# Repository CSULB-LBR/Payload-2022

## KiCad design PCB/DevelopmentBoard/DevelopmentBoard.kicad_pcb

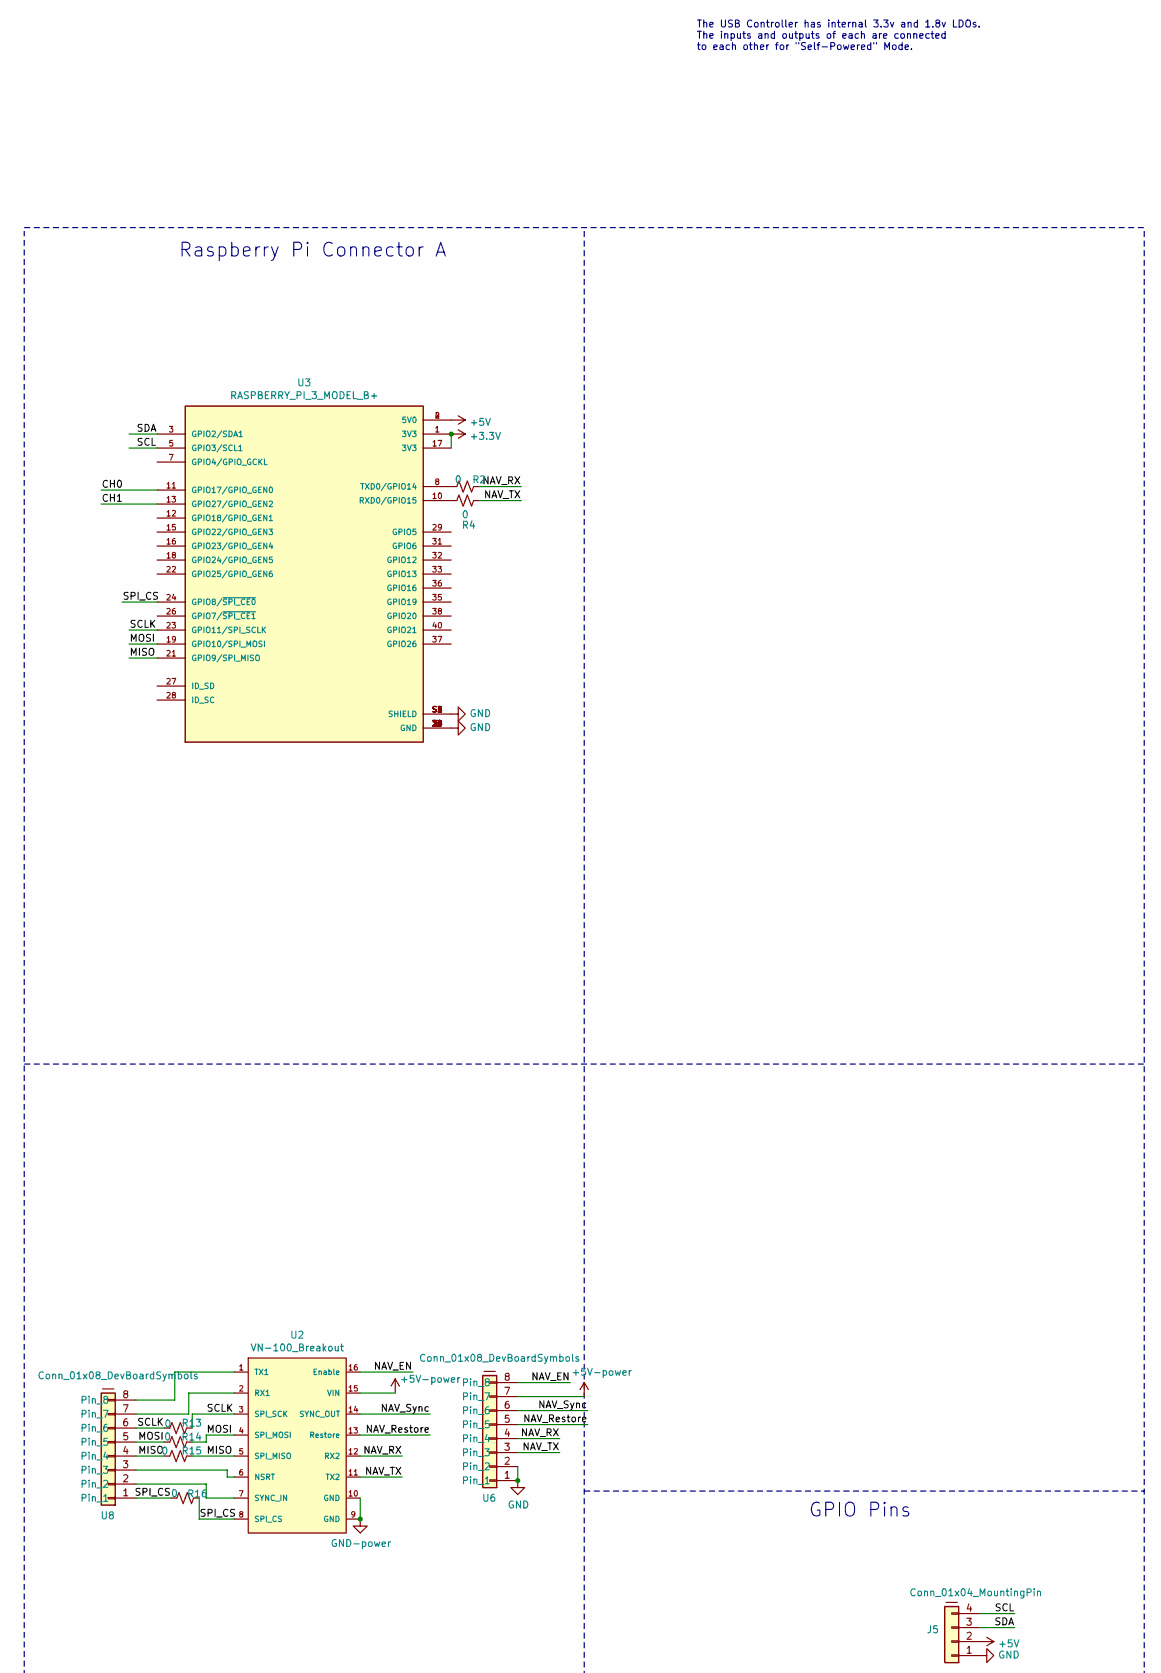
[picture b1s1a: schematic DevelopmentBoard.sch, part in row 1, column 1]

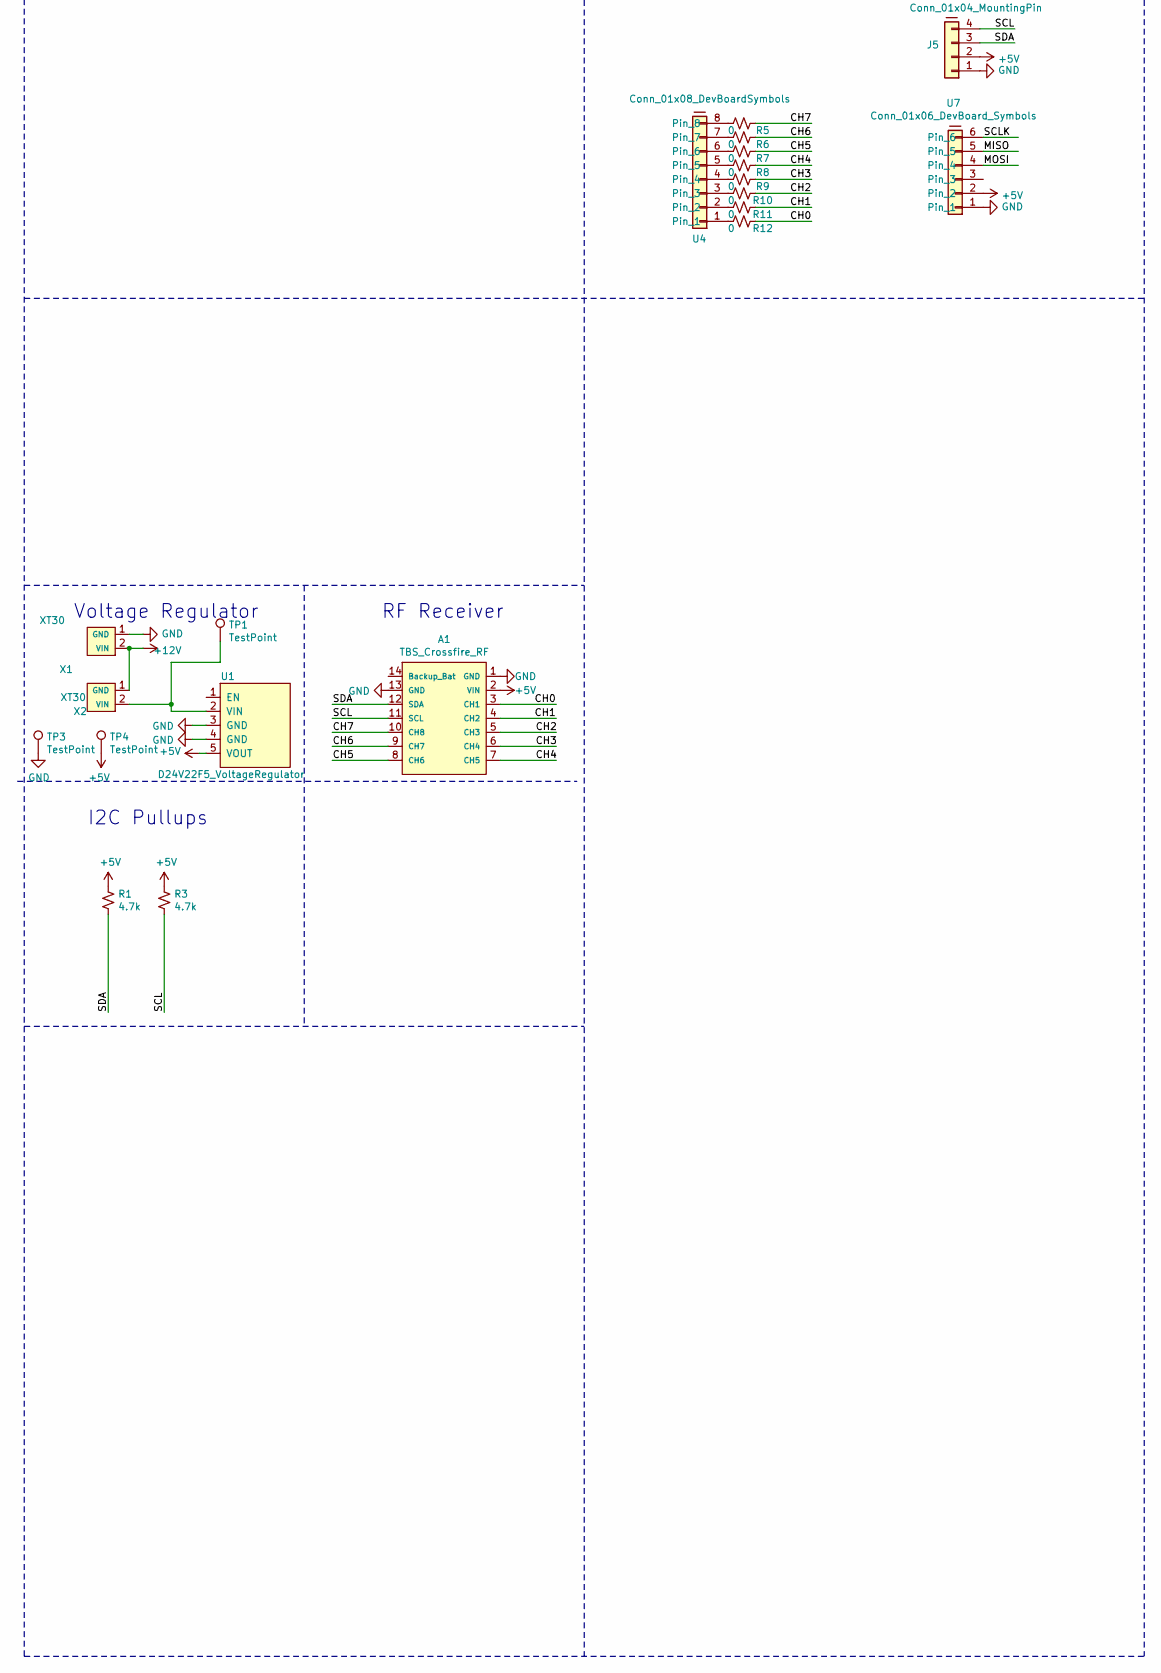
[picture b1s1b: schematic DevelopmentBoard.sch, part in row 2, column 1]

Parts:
A1: TBS_Crossfire_RF
J5: Conn_01x04_MountingPin; PinHeader_1x04_P2.54mm_Vertical
R1, R3: 4.7k; 0603
R2, R4, R5, R6, R7, R8, R9, R10, R11, R12, R13, R14, R15, R16: 0; 0603
TP1, TP3, TP4: TestPoint; TestPoint_Pad_D2.5mm
U1: D24V22F5_VoltageRegulator
U2: VN-100_Breakout; VN-100Breakout
U3: RASPBERRY_PI_3_MODEL_B+; MODULE_RASPBERRY_PI_3_MODEL_B+; PARTREV 1.0
U4, U6, U8: Conn_01x08_DevBoardSymbols; PinHeader_1x08_P2.54mm_Vertical
U7: Conn_01x06_DevBoard_Symbols; PinHeader_1x06_P2.54mm_Vertical
X1, X2: XT30; AMASS_XT30U-M_1x02_P5.0mm_Vertical

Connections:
+3V3: U3.1 (3V3), U3.17 (3V3)
+12V: X1.2 (VIN), X2.1 (GND)
/CH0: A1.3 (CH1), R12.2, U3.11 (GPIO17/GPIO_GEN0)
/CH1: A1.4 (CH2), R11.2, U3.13 (GPIO27/GPIO_GEN2)
/CH2: A1.5 (CH3), R10.2
/CH3: A1.6 (CH4), R9.2
/CH4: A1.7 (CH5), R8.2
/CH5: A1.8 (CH6), R7.2
/CH6: A1.9 (CH7), R6.2
/CH7: A1.10 (CH8), R5.2
/MISO: R15.1, R15.2, U2.5 (SPI_MISO), U3.21 (GPIO9/SPI_MISO), U7.5, U8.4
/MOSI: R14.1, R14.2, U2.4 (SPI_MOSI), U3.19 (GPIO10/SPI_MOSI), U7.4, U8.5
/NAV_EN: U2.16 (Enable), U6.8
/NAV_RX: R2.1, U2.12 (RX2), U6.4
/NAV_Restore: U2.13 (Restore), U6.5
/NAV_Sync: U2.14 (SYNC_OUT), U6.6
/NAV_TX: R4.1, U2.11 (TX2), U6.3
/SCL: A1.11 (SCL), J5.4, R3.2, U3.5 (GPIO3/SCL1)
/SCLK: R13.1, R13.2, U2.3 (SPI_SCK), U3.23 (GPIO11/SPI_SCLK), U7.6, U8.6
/SDA: A1.12 (SDA), J5.3, R1.2, U3.3 (GPIO2/SDA1)
/SPI_CS: R16.1, R16.2, U2.8 (SPI_CS), U3.24 (GPIO8/~SPI_CE0~), U8.1
unnamed: R2.2, U3.8 (TXD0/GPIO14)
unnamed: R4.2, U3.10 (RXD0/GPIO15)
unnamed: R5.1, U4.8
unnamed: R6.1, U4.7
unnamed: R7.1, U4.6
unnamed: R8.1, U4.5
unnamed: R9.1, U4.4
unnamed: R10.1, U4.3
unnamed: R11.1, U4.2
unnamed: R12.1, U4.1
unnamed: TP1.1, U1.2 (VIN), X2.2 (VIN)
unnamed: U2.1 (TX1), U8.8
unnamed: U2.2 (RX1), U8.7
unnamed: U2.6 (NSRT), U8.3
unnamed: U2.7 (SYNC_IN), U8.2

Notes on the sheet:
The USB Controller has internal 3.3v and 1.8v LDOs. The inputs and outputs of each are connected to each other for "Self-Powered" Mode.
Raspberry Pi Connector A
Voltage Regulator
RF Receiver
GPIO Pins
I2C Pullups

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
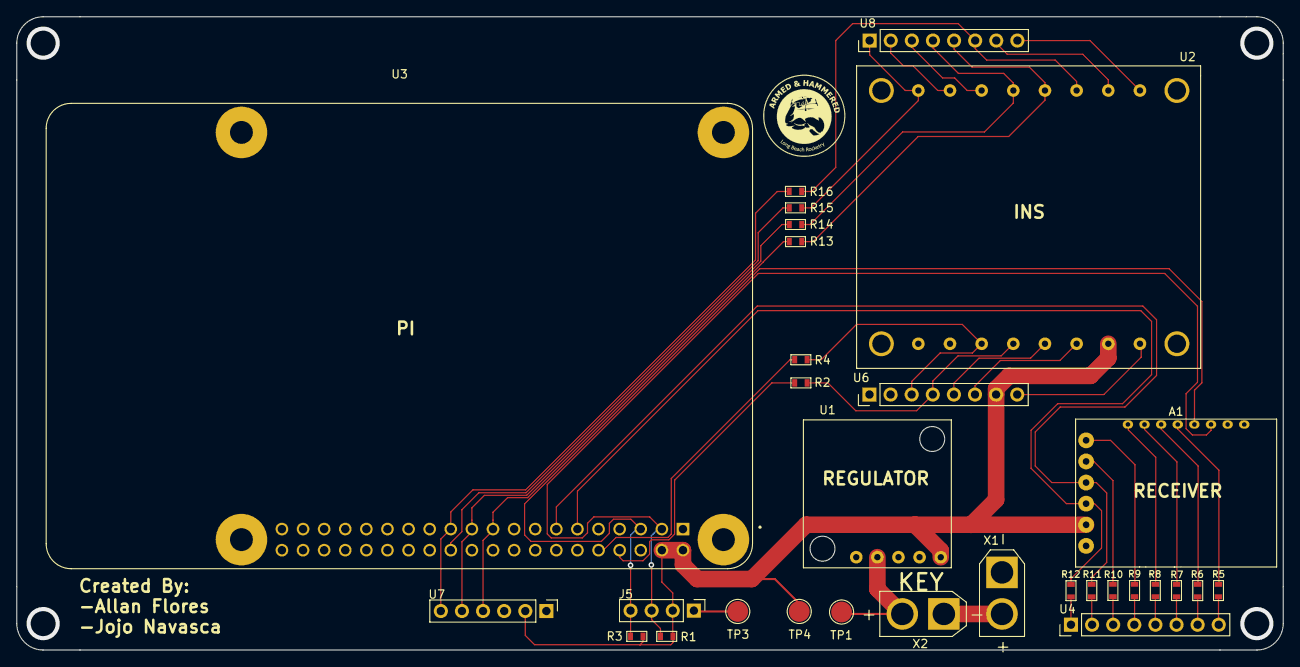
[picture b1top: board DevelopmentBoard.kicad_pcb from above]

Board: 2 copper layers, 152.4 x 76.2 mm, 30 parts (0 on the bottom side), 38 nets.

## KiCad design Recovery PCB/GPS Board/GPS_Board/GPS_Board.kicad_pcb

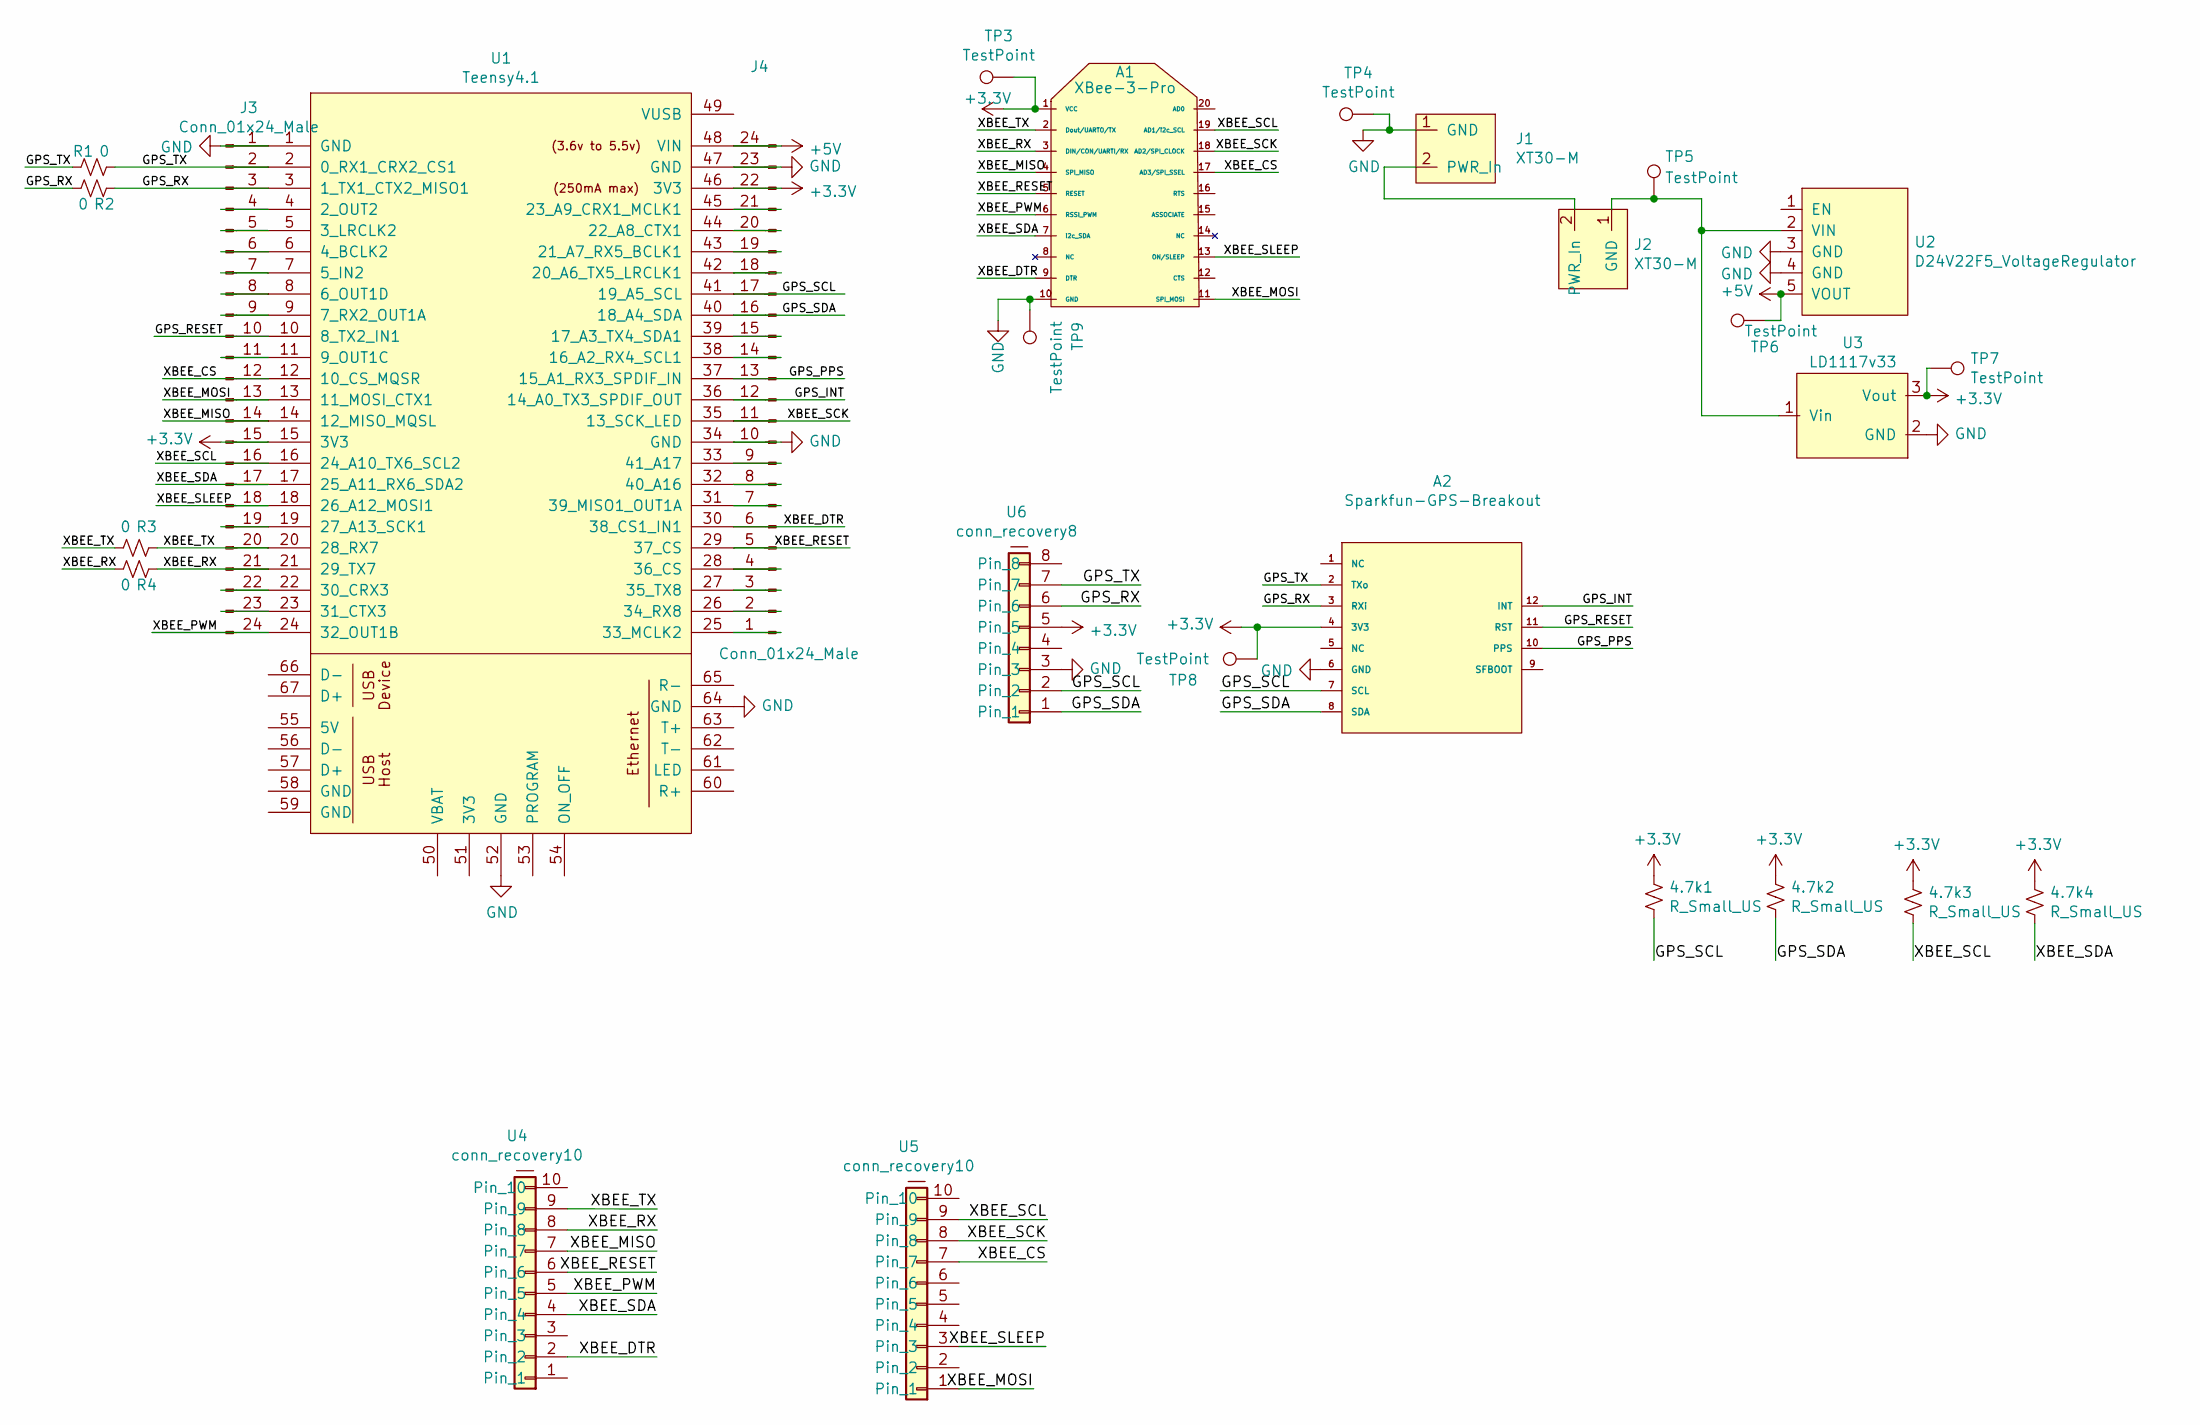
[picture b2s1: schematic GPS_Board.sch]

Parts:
4.7k1, 4.7k2, 4.7k3, 4.7k4: R_Small_US; 0603
A1: XBee-3-Pro; XBEE-20_THT
A2: Sparkfun-GPS-Breakout; Sparkfun-GPS-ZOE-M8Q-Breakout
J1, J2: XT30-M; AMASS_XT30U-M_1x02_P5.0mm_Vertical
J3, J4: Conn_01x24_Male; SMD_Connector_1x24
R1, R2: 0; 0603
R3, R4: 0; 0603_BACK
TP3, TP4, TP5, TP6, TP7, TP8, TP9: TestPoint; TestPoint_Pad_D2.0mm
U1: Teensy4.1; Teensy41
U2: D24V22F5_VoltageRegulator
U3: LD1117v33; TO-220-3_Horizontal_TabDown
U4, U5: conn_recovery10; PinHeader_1x10_P2.54mm_Vertical
U6: conn_recovery8; PinHeader_1x08_P2.54mm_Vertical

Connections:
+3V3: 4.7k1.1, 4.7k2.1, 4.7k3.1, 4.7k4.1, A1.1 (VCC), A2.4 (3V3), J3.15, J4.22, TP3.1, TP7.1, TP8.1, U1.15 (3V3), U1.46 (3V3), U3.3 (Vout), U6.5
+5V: J4.24, TP6.1, U1.48 (VIN), U2.5 (VOUT)
/GPS_INT: A2.12 (INT), J4.12, U1.36 (14_A0_TX3_SPDIF_OUT)
/GPS_PPS: A2.10 (PPS), J4.13, U1.37 (15_A1_RX3_SPDIF_IN)
/GPS_RESET: A2.11 (RST), J3.10, U1.10 (8_TX2_IN1)
/GPS_RX: A2.3 (RXi), J3.3, R2.1, R2.2, U1.3 (1_TX1_CTX2_MISO1), U6.6
/GPS_SCL: 4.7k1.2, A2.7 (SCL), J4.17, U1.41 (19_A5_SCL), U6.2
/GPS_SDA: 4.7k2.2, A2.8 (SDA), J4.16, U1.40 (18_A4_SDA), U6.1
/GPS_TX: A2.2 (TXo), J3.2, R1.1, R1.2, U1.2 (0_RX1_CRX2_CS1), U6.7
/XBEE_CS: A1.17 (AD3/SPI_SSEL), J3.12, U1.12 (10_CS_MQSR), U5.7
/XBEE_DTR: A1.9 (DTR), J4.6, U1.30 (38_CS1_IN1), U4.2
/XBEE_MISO: A1.4 (SPI_MISO), J3.14, U1.14 (12_MISO_MQSL), U4.7
/XBEE_MOSI: A1.11 (SPI_MOSI), J3.13, U1.13 (11_MOSI_CTX1), U5.1
/XBEE_PWM: A1.6 (RSSI_PWM), J3.24, U1.24 (32_OUT1B), U4.5
/XBEE_RESET: A1.5 (RESET), J4.5, U1.29 (37_CS), U4.6
/XBEE_RX: A1.3 (DIN/CON/UARTI/RX), J3.21, R4.1, R4.2, U1.21 (29_TX7), U4.8
/XBEE_SCK: A1.18 (AD2/SPI_CLOCK), J4.11, U1.35 (13_SCK_LED), U5.8
/XBEE_SCL: 4.7k3.2, A1.19 (AD1/i2c_SCL), J3.16, U1.16 (24_A10_TX6_SCL2), U5.9
/XBEE_SDA: 4.7k4.2, A1.7 (i2c_SDA), J3.17, U1.17 (25_A11_RX6_SDA2), U4.4
/XBEE_SLEEP: A1.13 (ON/SLEEP), J3.18, U1.18 (26_A12_MOSI1), U5.3
/XBEE_TX: A1.2 (Dout/UARTO/TX), J3.20, R3.1, R3.2, U1.20 (28_RX7), U4.9
GND: A1.10 (GND), A2.6 (GND), J1.1 (GND), J3.1, J4.10, J4.23, TP4.1, TP9.1, U1.1 (GND), U1.34 (GND), U1.47 (GND), U1.52 (GND), U1.64 (GND), U2.3 (GND), U2.4 (GND), U3.2 (GND), U6.3
unnamed: J1.2 (PWR_In), J2.2 (PWR_In)
unnamed: J2.1 (GND), TP5.1, U2.2 (VIN), U3.1 (Vin)
unnamed: J3.4, U1.4 (2_OUT2)
unnamed: J3.5, U1.5 (3_LRCLK2)
unnamed: J3.6, U1.6 (4_BCLK2)
unnamed: J3.7, U1.7 (5_IN2)
unnamed: J3.8, U1.8 (6_OUT1D)
unnamed: J3.9, U1.9 (7_RX2_OUT1A)
unnamed: J3.11, U1.11 (9_OUT1C)
unnamed: J3.19, U1.19 (27_A13_SCK1)
unnamed: J3.22, U1.22 (30_CRX3)
unnamed: J3.23, U1.23 (31_CTX3)
unnamed: J4.1, U1.25 (33_MCLK2)
unnamed: J4.2, U1.26 (34_RX8)
unnamed: J4.3, U1.27 (35_TX8)
unnamed: J4.4, U1.28 (36_CS)
unnamed: J4.7, U1.31 (39_MISO1_OUT1A)
unnamed: J4.8, U1.32 (40_A16)
unnamed: J4.9, U1.33 (41_A17)
unnamed: J4.14, U1.38 (16_A2_RX4_SCL1)
unnamed: J4.15, U1.39 (17_A3_TX4_SDA1)
unnamed: J4.18, U1.42 (20_A6_TX5_LRCLK1)
unnamed: J4.19, U1.43 (21_A7_RX5_BCLK1)
unnamed: J4.20, U1.44 (22_A8_CTX1)
unnamed: J4.21, U1.45 (23_A9_CRX1_MCLK1)

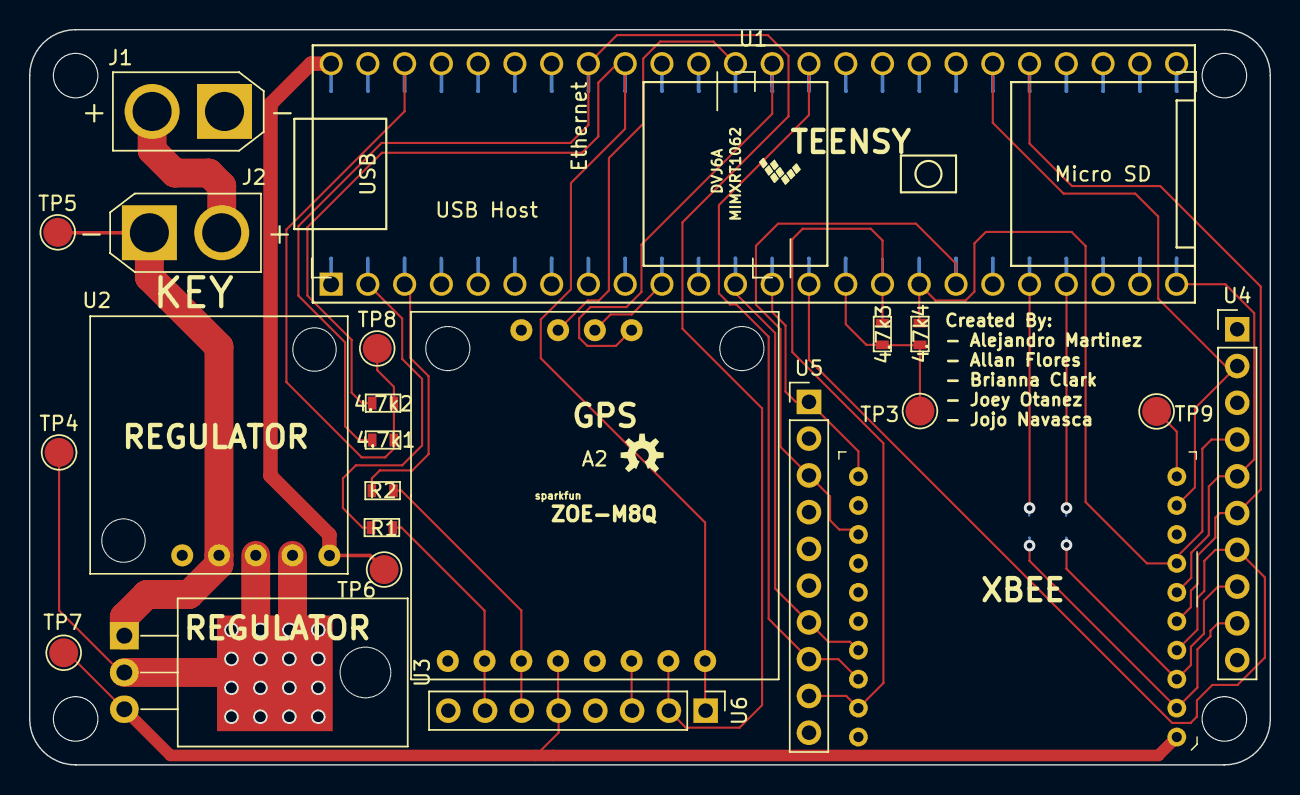
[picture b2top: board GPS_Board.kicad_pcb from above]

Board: 2 copper layers, 85.7 x 50.8 mm, 27 parts (0 on the bottom side), 47 nets.

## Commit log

2021-10-01 initial folder structure
2021-10-01 Created FlightBoard folder
2021-10-02 VN-100
    Made VN-100 Symbol
2021-10-02 d24v22f5 symbol added
2021-10-02 Deleted test symbols
2021-10-04 Relabeled GND on Voltage Regulator Symbol
2021-10-04 Added Voltage Regulator footprint
2021-10-04 Started VN-100 Footprint
2021-10-04 Added ground pin to Polololololol Board :)
2021-10-04 Pololooooo board for 6th ground pin dimension verified
2021-10-04 Labeled VN-100 Footprint Pins
2021-10-04 Added missing pins to VN-100 footprint
2021-10-04 Finished all pins for VN-100
2021-10-05 Added XT30 and TBS RF Module symbols and footprints
2021-10-05 FIx XT-30
    Changed gnd number
2021-10-07 Added Micro-USB and Pi CM4 symbol, and Pi CM4 footprint
2021-10-07 Micro USB
    Adjusted Micro USB symbol
2021-10-07 Edited PI CM4 symbol
2021-10-07 Started schematic capture
2021-10-07 Schematic Capture for RF module
2021-10-07 Placed Micro-USB symbol on schematic
2021-10-07 Deleted redundant RPI symbol library
2021-10-07 USB Pins
    Found and connected the USB pins on pins 103 & 105
2021-10-09 Created VN-100 Breakout project
2021-10-09 Cleaned up VN-100 pins
    Removed some extra pins
2021-10-09 Barometer
    Added Barometer Symbol
2021-10-09 Altimeter
    Added footprint of Altimeter with screholes
2021-10-10 Testing potential layout for board
2021-10-10 Updated pin numbering on VN-100 Breakout symbol
2021-10-11 Updated Altimeter/Barometer footprint, started VN-100 Breakout schematic capture
2021-10-11 VN-100 Breakout Created Label Connection
2021-10-12 VN-100 Board Layout started
2021-10-12 VN-100 edited
    Connected some traces in VN-100
2021-10-12 Reworked some traces from Martin
2021-10-12 Connected ground to pads
2021-10-12 Finished VN-100 Breakout Board. Removed USB from DevBoard Schematic
2021-10-13 Updated Dev Board Schematic
2021-10-13 Devboard changes(UART & SPI)
2021-10-13 Started Dev Board Layout
2021-10-13 Routed Test Traces for important signals
2021-10-13 Moved Altimeter and RF module for better I2C routing
2021-10-13 Added test points
2021-10-13 Edited 5v Traces
    Edited 5v traces on PCB
2021-10-14 Readjusted traces
2021-10-14 Added footprint courtyards
2021-10-14 Created Courtyard Voltage Regulator
2021-10-14 Sized traces. Moved USB connector. Uncrossed all signals.
2021-10-14 PCB Traces checked
2021-10-15 Traced matched USB D+ and D-
2021-10-16 Adjusted USB traces
2021-10-16 Added Step Files for RF Module and Voltage Regulator
2021-10-16 Rematched traces with Differential Pair tool. Added Step Files.
2021-10-16 added cm4 step model to dev board
2021-10-16 file system modifications for multi user work and created vn-100 breakout step
2021-10-16 Update fp-info-cache
2021-10-16 Routed traces for updated VN-100 breakout
2021-10-16 Changed VN-100 Breakout
2021-10-16 fixed vn-100 layer count and fill
2021-10-16 vectornav logo but its fps killer
2021-10-16 cant get rid of fps killer ss
2021-10-16 recerting before fps killer
2021-10-16 repaired after logo incident
2021-10-16 Grounded Pi Compute Module
2021-10-16 adjusted vn breakout
2021-10-16 fixed vectornav logo stuff
2021-10-16 breakout 3d model
2021-10-16 Updated footprint and symbol path
2021-10-16 added silkscreening, board outline, and fixed vn-100 carrier socket,plus renders
    NEEDS A MEME
2021-10-16 added grove 3d model
2021-10-20 step file locations changed for compatibility
2021-10-22 adding ethernet and UART breakout shrinking width of board with necessary rearrangement
2021-10-22 giving up on ethernet for now, added a couple of open source breakout designs for reference
2021-10-23 changed models directory again
2021-10-23 ladybug happy :)
2021-10-23 ladybug more happier
2021-10-23 Reassociated 3D files
2021-10-23 revert
2021-10-23 got it to make a step file literally no idea how
2021-10-23 zippedupthedingus
2021-10-23 tidying
2021-10-27 credits
2021-12-02 Removed "PayloadSymbols" Folder, consolidated symbols and footprints into DevelopmentBoard Folder
2021-12-02 Added USB Controller symbol, footprint, and Step File
2021-12-02 Started adding USB Controller to schematic
2021-12-02 Schematic for USB-A ports and USB 2.0 Controller
2021-12-02 Added RJ45 Connector footprint and symbol
2021-12-02 Implemented Ethernet on Schematic
2021-12-02 Imported new components onto layout
2021-12-02 Basic layout with USB ports and ethernet
2021-12-02 Updated layout for USB Controller
2021-12-02 Adjusted USB-A Data traces
2021-12-03 Adjusted board layout
2021-12-03 Completed USB Controller, routed 5v trace
2021-12-03 Routed Ethernet Pairs
2021-12-03 Moved USB Jumper/0hm resistors
2021-12-03 Routed traces from VN-100 breakout
2021-12-03 Routed I2C traces
2021-12-03 Set I2C pullups
2021-12-03 Rerouted UART and SPI traces
2021-12-04 Eliminated perpendicular trace routing
2021-12-04 recovery PCB's will go here, including the GPS system connector board i just designed
2021-12-04 Trace matched Micro USB
2021-12-04 more recovery pcb shid
2021-12-04 Trace matched Second pair ethernet
2021-12-04 Ethernet Trace Matching
2021-12-04 Made more differential pairs the same
2021-12-05 Adjusted ethernet pair lengths
2021-12-05 Adjusted USB D0 trace thickness
2021-12-05 Traced matched USB controller
2021-12-05 Adjusted Backup USB
2021-12-05 Adjusted silkscreen text
2021-12-05 Added display pins
2021-12-05 Adjusted components for DRC check
2021-12-05 Added GND Plane
2021-12-05 Added 14 GPIO pins
2021-12-05 Routed half of GPIO pins
2021-12-05 Added GPIO traces
2021-12-05 Reimplemented GND plane
2021-12-05 Final adjustments
2021-12-05 Adjusted traces
2021-12-06 silkscreen improvements
2021-12-06 added extra graphics, still needs mounting holes replaced
2021-12-06 recovery board changes
2021-12-11 finally opened my laptop and pushing changes and gerbers i sent to JLC
2022-01-02 Relabelled RX/TX to RX1/TX1, RX2/TX2
2022-01-02 Set graphic lines on schematic
2022-01-02 Labelled sections on schematic
2022-01-02 Labelled and Sectioned Schematic
2022-01-02 Fixed routing error on crystal
2022-01-02 renderbusiness and ethernet model added
2022-01-02 more images
2022-01-05 reorganized a bit
2022-01-12 UART added
    Please check my work
2022-01-12 DOUT to 28 and DIN to 29
2022-01-14 Created Pi-CM4Stencil Project
2022-01-14 Created gerber files
2022-03-13 Added the edge cuts for the new PCB.
2022-03-13 Imported new symbol and footprint of Raspberry Pi 3 B+ for comparison on Raspberry Pi 4
2022-03-13 Started ADC symbol
2022-03-13 New Symbol and Footprint for MCP3008 ADC
2022-03-14 Simplified Schematic and added corrected symbols
2022-03-14 Updated Schematic and including wire routing between components
2022-03-14 Created Connector Symbol for MCP3008 ADC
2022-03-14 Created new footprints for components and setup a rough draft of component placements on board
2022-03-16 Routed signal traces from ADC to Crossfire receiver
2022-03-16 Routed traces for SPI and I2C to the Pi
2022-03-16 Revert "Created gerber files"
    This reverts commit b53c7857d78f5a39796a9ae11ef4b5de09c35e59.
2022-03-16 All traces routed
2022-03-16 Revert "Merge branch 'main' of https://github.com/CSULB-LBR/Payload-2022-Electrical"
    This reverts commit 36186b0aa135225f420ab8312ad97e4f675c68a7, reversing
    changes made to 173b9dac6d612d33aa589f2b9774fff44ddaf61c.
2022-03-16 Revert "Revert "Merge branch 'main' of https://github.com/CSULB-LBR/Payload-2022-Electrical""
    This reverts commit 1fa6b27fb9c3b41626163316b63d82927b4b0d34.
2022-03-16 Revert "All traces routed"
    This reverts commit c95ed1feddb0a668cbf08043fd846f3cc9ac1831.
2022-03-16 Overwrite files.
2022-03-17 Adjusted board edge cuts and added mounting holes
2022-03-17 Added Copper fill to back layer of PCB.
2022-03-17 Added 3.3V testpoint
2022-03-17 Rewired I2C Pins on the Pi
2022-03-17 Adjusted traces.
2022-03-17 Added I2C Outputs on the TBS Module
2022-03-17 FInal Tracing changes and Copper Refill.
2022-03-17 Adjusted some traces and silkscreen locations
2022-03-17 Added names to silkscreen
2022-03-17 Moved references
2022-03-17 added snek footprint file
2022-03-17 Added front and back silk screen.
2022-04-12 Updating GPS breakout Schematic
2022-04-12 Labeled connections from GPS to teensy
2022-04-12 Labels for GPS
2022-04-13 XBEE Labels
2022-04-14 test push
2022-04-14 Label Stuff
2022-04-14 testing
2022-04-14 replace all wires w labels
2022-04-14 replace wires w labels
2022-04-14 Updated Xbee Symbol and font
2022-04-14 Changed some labels
2022-04-14 Adjusted XBEE labels, and symbol
2022-04-14 Added regulator symbols
2022-04-14 Added footprint to 3.3v regulator
2022-04-15 Added UART labels and testpoints
2022-04-15 Fixed GPS symbol
2022-04-15 Schematic look over
2022-04-15 Created netlist
2022-04-15 Initial Board Layout
2022-04-15 Power Traces Outline
2022-04-15 Did row of traces from Teensy
2022-04-15 bris changes
2022-04-15 Finished More Traces
2022-04-15 Fixed power routing
2022-04-15 Routed data traces from GPS
2022-04-15 Adjusted path substitution
2022-04-15 changed Xbee footprint
2022-04-15 Routed all traces and removed vias
2022-04-15 Added pad for heat dissipation
2022-04-16 Added NAV route to breakout
2022-04-16 initial board layout and traces
2022-04-16 Routed all traces
2022-04-16 Routed TBS connector
2022-04-16 Added breakouts pins for INS
2022-04-16 Added connectors and updated traces.
2022-04-16 Added payload logo
2022-04-17 Created SMD Breakout Pins
2022-04-17 Added teensy breakout pads
2022-04-17 Added Silkscreen doge
2022-04-17 Added silkscreen
2022-04-17 Fixed silkscreen
2022-04-17 Added 0 ohm resistors
2022-04-17 Moved 3.3v Trace
2022-04-17 Changed 0 ohm resistor locations
2022-04-17 Removed testpoint
2022-04-17 Silkscreened and final trace adjustments
2022-04-17 Added 0 ohm resistors on backside
2022-04-17 Created GBR files for Recovery PCB
2022-04-17 Generated Payload PCB GBR files
2022-04-17 Created Gerber Zips
